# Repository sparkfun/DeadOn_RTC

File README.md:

DeadOn RTC-DS3234 Breakout Board
==========

[*DeadOn RTC- DS3234 Breakout (BOB-10160)*](https://www.sparkfun.com/products/10160)

This is a real time clock based on the DS3234 Real Time Clock IC. The DS3234  is a low-cost, extremely accurate SPI bus real-time clock with an integrated temperature-compensated crystal oscillator and crystal.

Repository Contents
-------------------
* **/Hardware** - All Eagle design files (.brd, .sch)
* **/Libraries** - All Arduino libraries and board examples

Version History
---------------

* [V_1.2.1](https://github.com/sparkfun/DeadOn_RTC/tree/V_1.2.1) - Pulled latest library
* [V_1.2.0](https://github.com/sparkfun/DeadOn_RTC/tree/V_1.2.0) - Updated to new library structure 
* [V_1.1](https://github.com/sparkfun/DeadOn_RTC/tree/v1.1) - Original structure

License Information
-------------------
The hardware is released under [Creative Commons Share-alike 3.0](http://creativecommons.org/licenses/by-sa/3.0/).  
All other code is open source so please feel free to do anything you want with it; you buy me a beer if you use this and we meet someday ([Beerware license](http://en.wikipedia.org/wiki/Beerware)).

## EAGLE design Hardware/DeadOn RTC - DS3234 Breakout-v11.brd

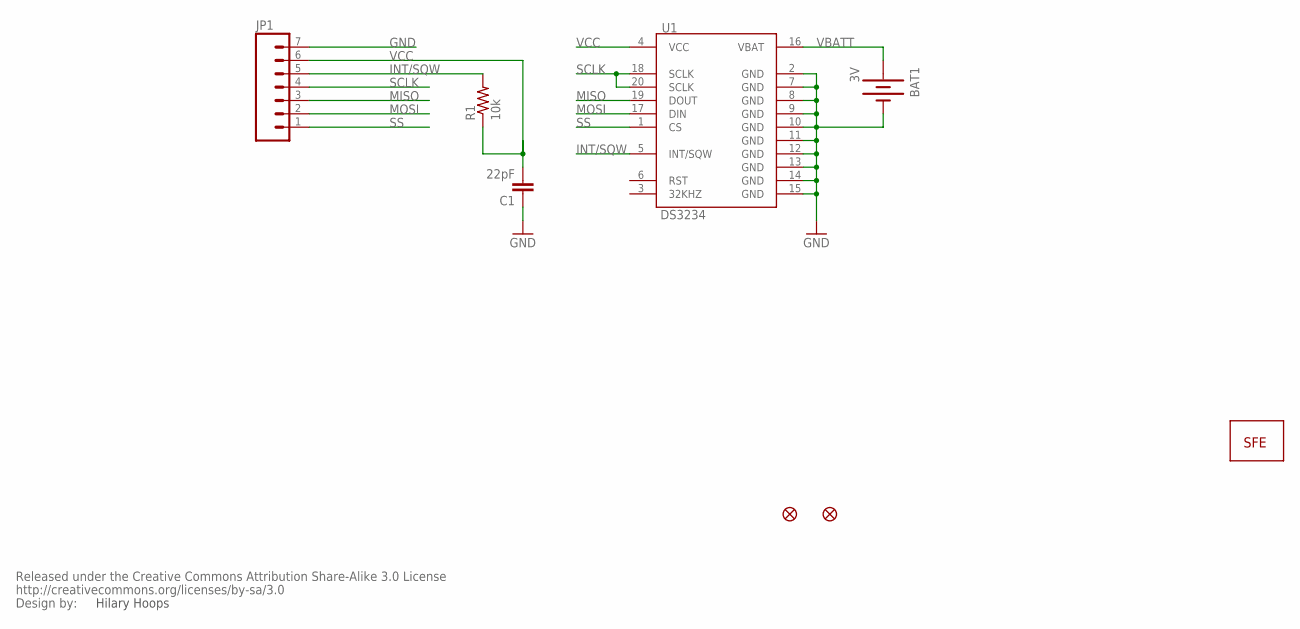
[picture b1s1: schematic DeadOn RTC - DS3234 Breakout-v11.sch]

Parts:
BAT1: 3V; BATTCON_12MM_CURVED
C1: 22pF; 0402-CAP
JP1: M07; 1X07
JP2: LOGO-SFESK; SFE-LOGO-FLAME
JP3, JP4: FIDUCIAL1X2; FIDUCIAL-1X2
R1: 10k; 0402-RES
U1: DS3234
U$1: CREATIVE_COMMONS

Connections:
GND: BAT1.GND (-), C1.1, JP1.7, U1.2 (GND), U1.7 (GND), U1.8 (GND), U1.9 (GND), U1.10 (GND), U1.11 (GND), U1.12 (GND), U1.13 (GND), U1.14 (GND), U1.15 (GND)
INT/SQW: JP1.5, R1.2, U1.5 (INT/SQW)
MISO: JP1.3, U1.19 (DOUT)
MOSI: JP1.2, U1.17 (DIN)
SCLK: JP1.4, U1.18 (SCLK), U1.20 (SCLK)
SS: JP1.1, U1.1 (CS)
VBATT: BAT1.PWR@1 (+), U1.16 (VBAT)
VCC: C1.2, JP1.6, R1.1, U1.4 (VCC)

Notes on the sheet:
Hilary Hoops

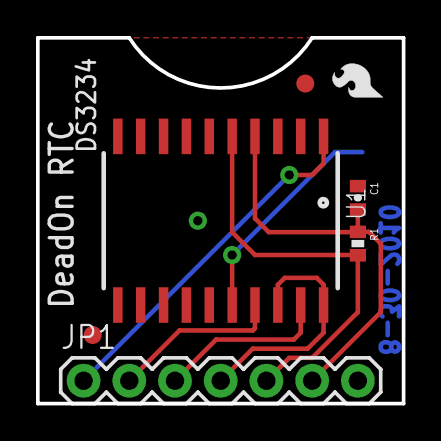
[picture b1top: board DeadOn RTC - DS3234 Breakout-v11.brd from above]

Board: 2 copper layers, 20.3 x 20.3 mm, 9 parts (1 on the bottom side), 8 nets.

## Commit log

2013-08-05 Initial commit of board/code files
2013-08-05 Adding .gitignore
2014-06-10 Typo fix: "DS32234" to "DS3234"
    Nitpick but why not!
2014-07-22 Applying https://github.com/sparkfun/DeadOn_RTC/commit/c39db0e3e531938815ec6113d6a0f4283dbe55c0
2014-07-22 Fix directory structure and naming convention.
    This allows a user to git clone/zip-download the repo and then move/copy/symlink
    the Libraries/DeadOn_RTC directory into ~/Documents/Arduino/Libraries/ and have
    the example show up correctly.
2015-04-26 Squashed 'Libraries/Arduino/' content from commit 0ec50ac
    git-subtree-dir: Libraries/Arduino
    git-subtree-split: 0ec50ac65814e820e83f5cb2c3d875f167149009
2015-04-26 Updating to new library structure
2015-04-26 fixed formatting
2015-04-26 Added version ref
2015-04-26 fixed version section again
2015-04-29 Squashed 'Libraries/Arduino/' content from commit e3c67c2
    git-subtree-dir: Libraries/Arduino
    git-subtree-split: e3c67c25f2b050ad40c8a487617e7b2fc0740251
2025-06-27 Update README.md
    Updating link

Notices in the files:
parts and their libraries:
SparkFun: Released under the Creative Commons Attribution Share-Alike 3.0 License
